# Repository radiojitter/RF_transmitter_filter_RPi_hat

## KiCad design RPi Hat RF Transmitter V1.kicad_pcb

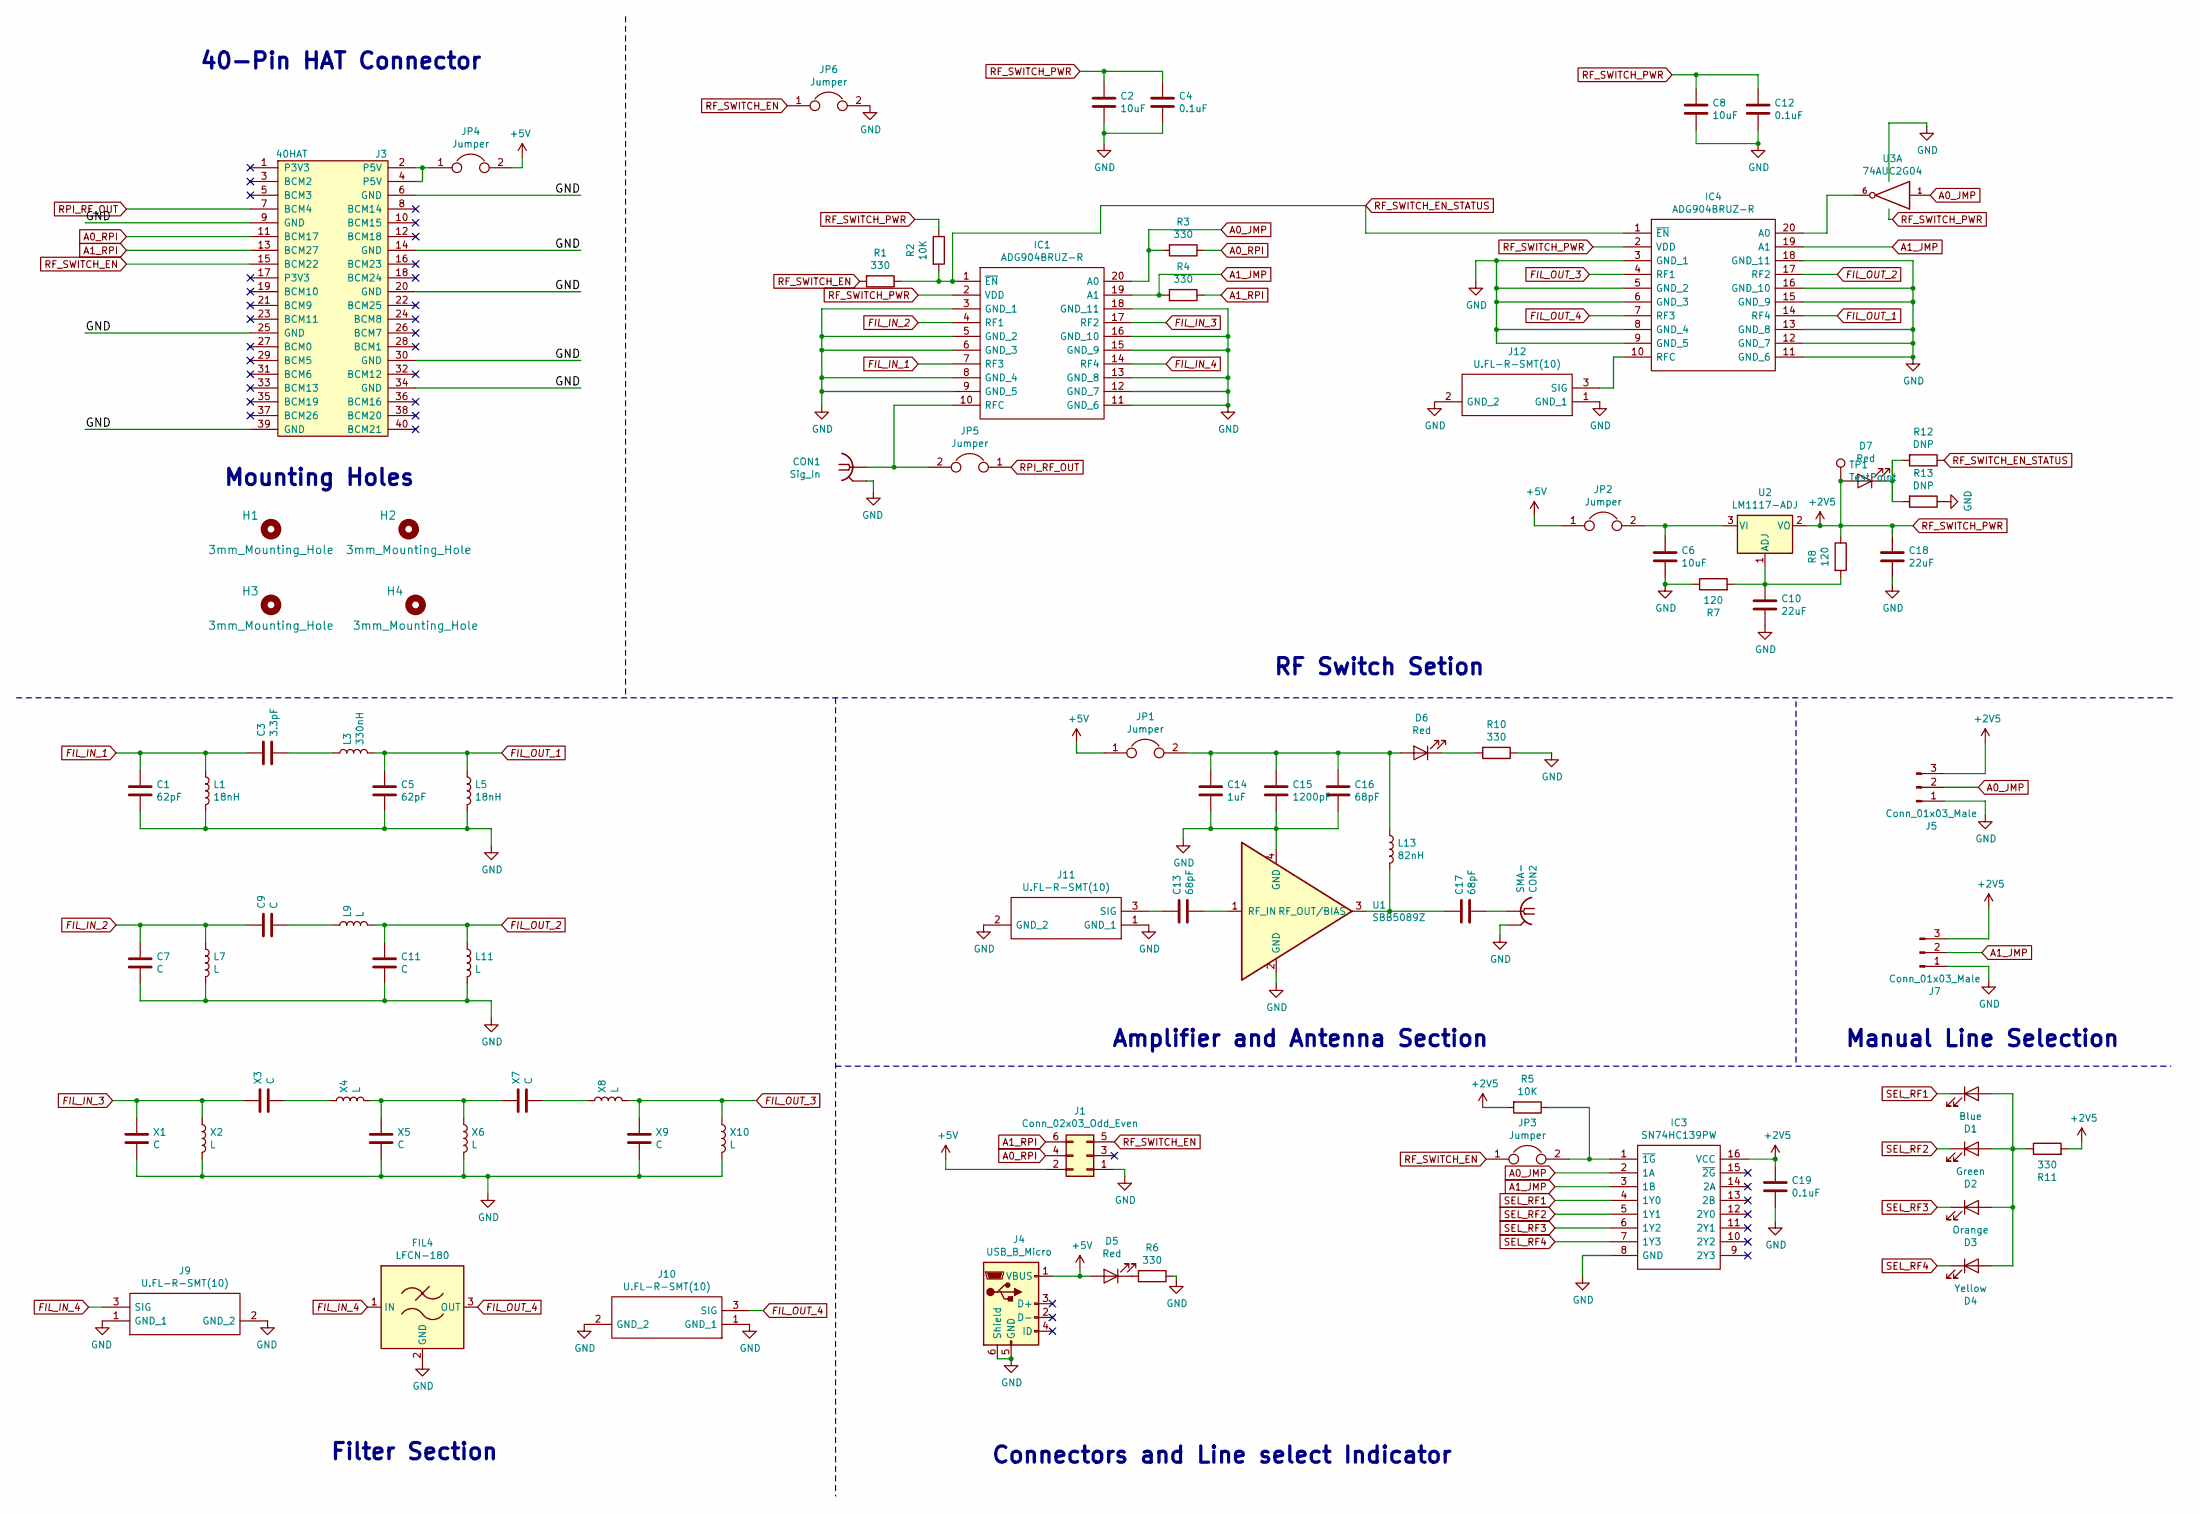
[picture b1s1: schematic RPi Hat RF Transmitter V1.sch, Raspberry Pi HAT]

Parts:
C1, C5: 62pF; C_0805_2012Metric_Pad1.15x1.40mm_HandSolder
C2, C8: 10uF; C_0805_2012Metric_Pad1.15x1.40mm_HandSolder
C3: 3.3pF; C_0805_2012Metric_Pad1.15x1.40mm_HandSolder
C4, C12, C19: 0.1uF; C_0805_2012Metric_Pad1.15x1.40mm_HandSolder
C6: 10uF; C_1206_3216Metric_Pad1.42x1.75mm_HandSolder
C7, C9, C11: C; C_0805_2012Metric_Pad1.15x1.40mm_HandSolder
C10, C18: 22uF; C_1206_3216Metric_Pad1.42x1.75mm_HandSolder
C13, C16, C17: 68pF; C_0805_2012Metric_Pad1.15x1.40mm_HandSolder
C14: 1uF; C_0805_2012Metric_Pad1.15x1.40mm_HandSolder
C15: 1200pF; C_0805_2012Metric_Pad1.15x1.40mm_HandSolder
CON1: Sig_In; SMA_Amphenol_132291-12_Vertical
CON2: SMA-; SMA_Amphenol_132291-12_Vertical
D1: Blue; LED_0805_2012Metric_Pad1.15x1.40mm_HandSolder
D2: Green; LED_0805_2012Metric_Pad1.15x1.40mm_HandSolder
D3: Orange; LED_0805_2012Metric_Pad1.15x1.40mm_HandSolder
D4: Yellow; LED_0805_2012Metric_Pad1.15x1.40mm_HandSolder
D5, D6, D7: Red; LED_0805_2012Metric_Pad1.15x1.40mm_HandSolder
FIL4: LFCN-180; Filter_Mini-Circuits_FV1206
H1, H2, H3, H4: 3mm_Mounting_Hole; NPTH_3mm_ID
IC1, IC4: ADG904BRUZ-R; SOP65P640X120-20N; Mouser Part Number 584-ADG904BRUZ-R
IC3: SN74HC139PW; SOIC-16_3.9x9.9mm_P1.27mm; Mouser Part Number 595-SN74HC139PW
J1: Conn_02x03_Odd_Even; PinHeader_2x03_P2.54mm_Vertical
J3: 40HAT; PinSocket_2x20_P2.54mm_Vertical
J4: USB_B_Micro; USB_Micro-B_Molex-105017-0001
J5, J7: Conn_01x03_Male; PinHeader_1x03_P2.54mm_Vertical
J9, J10, J11, J12: U.FL-R-SMT(10); UFLRSMT10; Mouser Part Number 798-U.FL-R-SMT10
JP1, JP2, JP3, JP4, JP5, JP6: Jumper; PinHeader_1x02_P2.54mm_Vertical
L1, L5: 18nH; L_0805_2012Metric_Pad1.15x1.40mm_HandSolder
L3: 330nH; L_0805_2012Metric_Pad1.15x1.40mm_HandSolder
L7, L9, L11: L; L_0805_2012Metric_Pad1.15x1.40mm_HandSolder
L13: 82nH; L_0805_2012Metric_Pad1.15x1.40mm_HandSolder
R1, R3, R4, R6, R10, R11: 330; R_0805_2012Metric_Pad1.15x1.40mm_HandSolder
R2, R5: 10K; R_0805_2012Metric_Pad1.15x1.40mm_HandSolder
R7, R8: 120; R_0805_2012Metric_Pad1.15x1.40mm_HandSolder
R12, R13: DNP; R_0603_1608Metric
TP1: TestPoint; Pin_D0.9mm_L10.0mm_W2.4mm_FlatFork
U1: SBB5089Z
U2: LM1117-ADJ; SOT-223-3_TabPin2
U3: 74AUC2G04; SOT-23-6_Handsoldering
X1, X3, X5, X7, X9: C; C_0805_2012Metric_Pad1.15x1.40mm_HandSolder
X2, X4, X6, X8, X10: L; L_0805_2012Metric_Pad1.15x1.40mm_HandSolder

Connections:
+5V: D5.2 (A), J1.2, J4.1 (VBUS), JP1.1, JP2.1, JP4.2
A0_JMP: IC1.20 (A0), IC3.2 (1A), J5.2, R3.2, U3.1
A0_RPI: J1.4, J3.11 (BCM17), R3.1
A1_JMP: IC1.19 (A1), IC3.3 (1B), IC4.19 (A1), J7.2, R4.2
A1_RPI: J1.6, J3.13 (BCM27), R4.1
FIL_IN_1: C1.1, C3.1, IC1.7 (RF3), L1.1
FIL_IN_2: C7.1, C9.1, IC1.4 (RF1), L7.1
FIL_IN_3: IC1.17 (RF2), X1.1, X2.1, X3.1
FIL_IN_4: FIL4.1 (IN), IC1.14 (RF4), J9.3 (SIG)
FIL_OUT_1: C5.1, IC4.14 (RF4), L3.2, L5.1
FIL_OUT_2: C11.1, IC4.17 (RF2), L9.2, L11.1
FIL_OUT_3: IC4.4 (RF1), X8.2, X9.1, X10.1
FIL_OUT_4: FIL4.3 (OUT), IC4.7 (RF3), J10.3 (SIG)
GND: C1.2, C2.2, C4.2, C5.2, C6.2, C7.2, C8.2, C10.2, C11.2, C12.2, C14.2, C15.2, C16.2, C18.2, C19.2, CON1.2, CON2.2, FIL4.2 (GND), FIL4.4 (GND), IC1.3 (GND_1), IC1.5 (GND_2), IC1.6 (GND_3), IC1.8 (GND_4), IC1.9 (GND_5), IC1.11 (GND_6), IC1.12 (GND_7), IC1.13 (GND_8), IC1.15 (GND_9), IC1.16 (GND_10), IC1.18 (GND_11), IC3.8 (GND), IC4.3 (GND_1), IC4.5 (GND_2), IC4.6 (GND_3), IC4.8 (GND_4), IC4.9 (GND_5), IC4.11 (GND_6), IC4.12 (GND_7), IC4.13 (GND_8), IC4.15 (GND_9), IC4.16 (GND_10), IC4.18 (GND_11), J1.1, J3.6 (GND), J3.9 (GND), J3.14 (GND), J3.20 (GND), J3.25 (GND), J3.30 (GND), J3.34 (GND), J3.39 (GND), J4.5 (GND), J4.6 (Shield), J5.1, J7.1, J9.1 (GND_1), J9.2 (GND_2), J10.1 (GND_1), J10.2 (GND_2), J11.1 (GND_1), J11.2 (GND_2), J12.1 (GND_1), J12.2 (GND_2), JP6.2, L1.2, L5.2, L7.2, L11.2, R6.1, R7.1, R10.1, R13.1, U1.2 (GND), U1.4 (GND), U3.2 (GND), X1.2, X2.2, X5.2, X6.2, X9.2, X10.2
unnamed: C3.2, L3.1
unnamed: C6.1, JP2.2, U2.3 (VI)
unnamed: C9.2, L9.1
unnamed: C10.1, R7.2, R8.2, U2.1 (ADJ)
unnamed: C13.1, J11.3 (SIG)
unnamed: C13.2, U1.1 (RF_IN)
unnamed: C14.1, C15.1, C16.1, D6.2 (A), JP1.2, L13.1
unnamed: C17.1, L13.2, U1.3 (RF_OUT/BIAS)
unnamed: C17.2, CON2.1
unnamed: CON1.1, IC1.10 (RFC), JP5.2
unnamed: D1.2 (A), D2.2 (A), D3.2 (A), D4.2 (A), R11.1
unnamed: D5.1 (K), R6.2
unnamed: D6.1 (K), R10.2
unnamed: D7.1 (K), R12.2, R13.2
unnamed: IC3.1 (~1G), JP3.2, R5.1
unnamed: IC4.10 (RFC), J12.3 (SIG)
unnamed: IC4.20 (A0), U3.6
unnamed: J3.2 (P5V), J3.4 (P5V), JP4.1
unnamed: X3.2, X4.1
unnamed: X4.2, X5.1, X6.1, X7.1
unnamed: X7.2, X8.1
RF_SWITCH_EN: J1.5, J3.15 (BCM22), JP3.1, JP6.1, R1.2
RF_SWITCH_EN_STATUS: IC1.1 (~EN), IC4.1 (~EN), R1.1, R2.2, R12.1
RF_SWITCH_PWR: C2.1, C4.1, C8.1, C12.1, C18.1, C19.1, D7.2 (A), IC1.2 (VDD), IC3.16 (VCC), IC4.2 (VDD), J5.3, J7.3, R2.1, R5.2, R8.1, R11.2, TP1.1, U2.2 (VO), U3.5 (VCC)
RPI_RF_OUT: J3.7 (BCM4), JP5.1
SEL_RF1: D1.1 (K), IC3.4 (1Y0)
SEL_RF2: D2.1 (K), IC3.5 (1Y1)
SEL_RF3: D3.1 (K), IC3.6 (1Y2)
SEL_RF4: D4.1 (K), IC3.7 (1Y3)

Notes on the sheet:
Mounting Holes
40-Pin HAT Connector
Filter Section
RF Switch Setion
Amplifier and Antenna Section
Connectors and Line select Indicator
Manual Line Selection

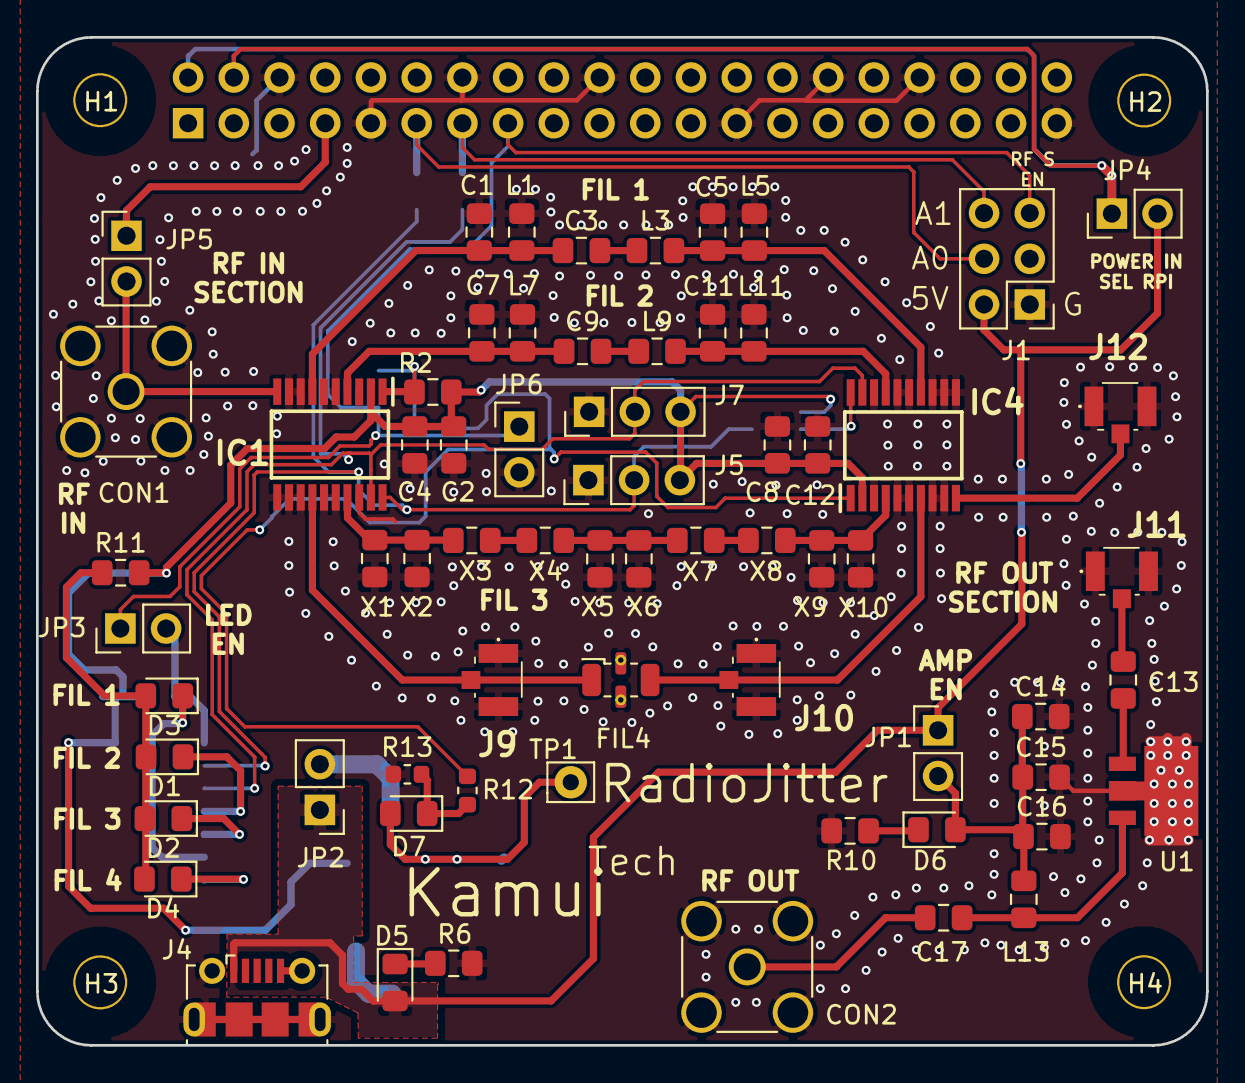
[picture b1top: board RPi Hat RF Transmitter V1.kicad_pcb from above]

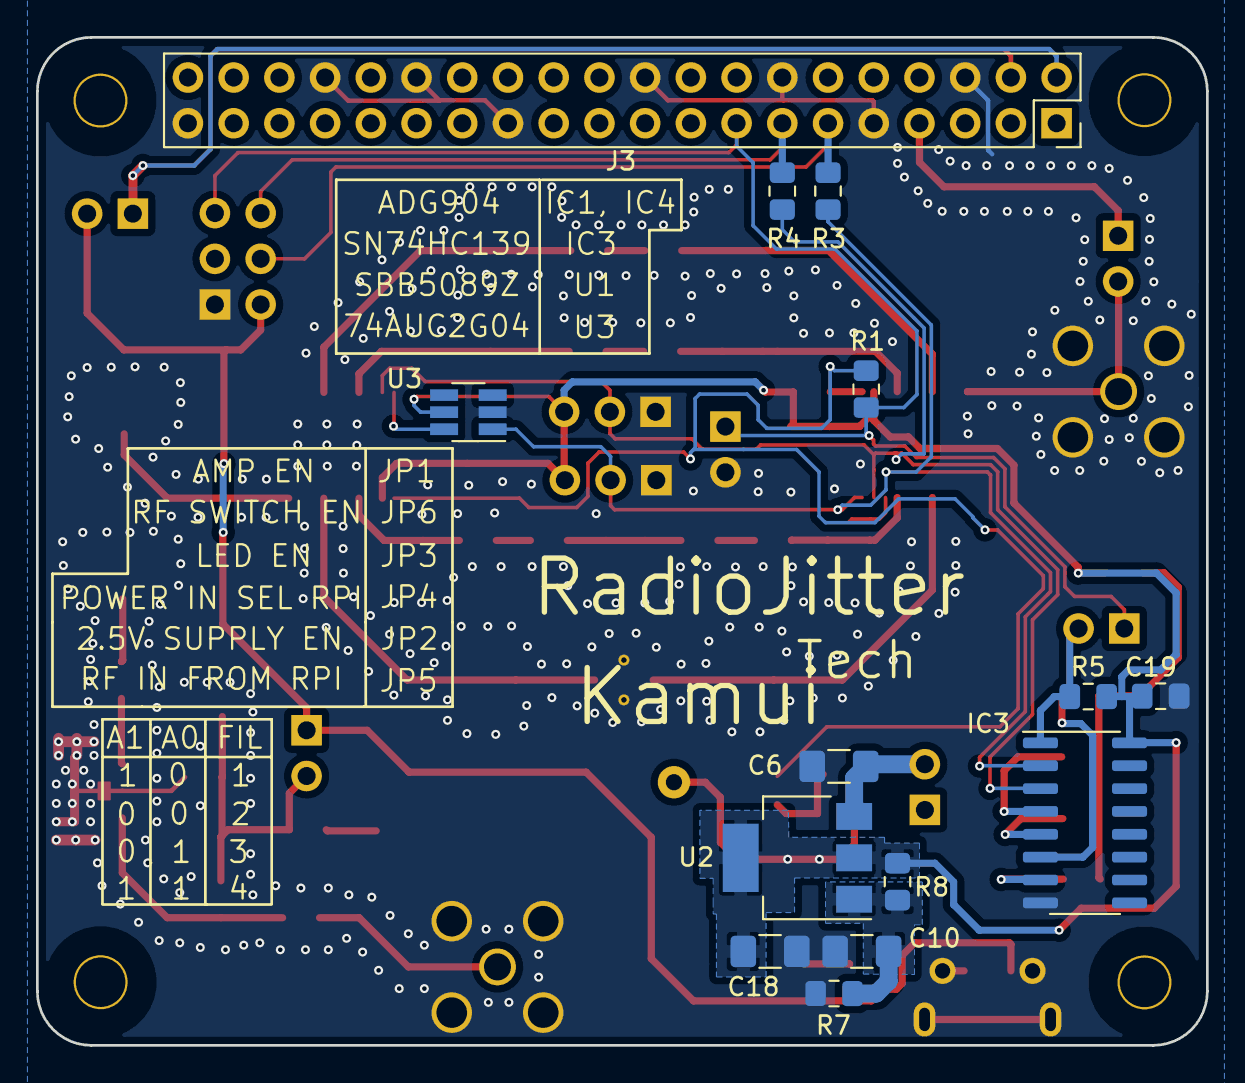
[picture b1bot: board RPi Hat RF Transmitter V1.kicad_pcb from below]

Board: 4 copper layers, 65.0 x 56.0 mm, 84 parts (14 on the bottom side), 43 nets.

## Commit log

2019-10-15 first commit, finished till last version
2019-10-19 changes the switch, adds LDO, adds Jumpers for RF lines, changes names of existing nets
2019-10-20 adds ufl connectors, now readymade filter at forth filter etc
2019-10-30 routed for new circuit
2019-10-30 minor save
2019-11-05 before generating GERBER
2019-11-05 adds silk screen updates, ground stiching and generated GERBERs
2019-11-05 V2 from here
